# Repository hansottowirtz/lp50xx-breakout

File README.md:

# Breakout board for LP5018 and LP5024

- Designed with Autodesk Eagle
- 2-layer board
- Builtin 0603 R_IREF and trimpot to control current, and 1uF 0603 C_VCAP.
- Uses [LP50XX Library](./lp50xx.lbr), modified [Sparkfun Libraries](https://github.com/sparkfun/SparkFun-Eagle-Libraries) and a modified pinhead library.

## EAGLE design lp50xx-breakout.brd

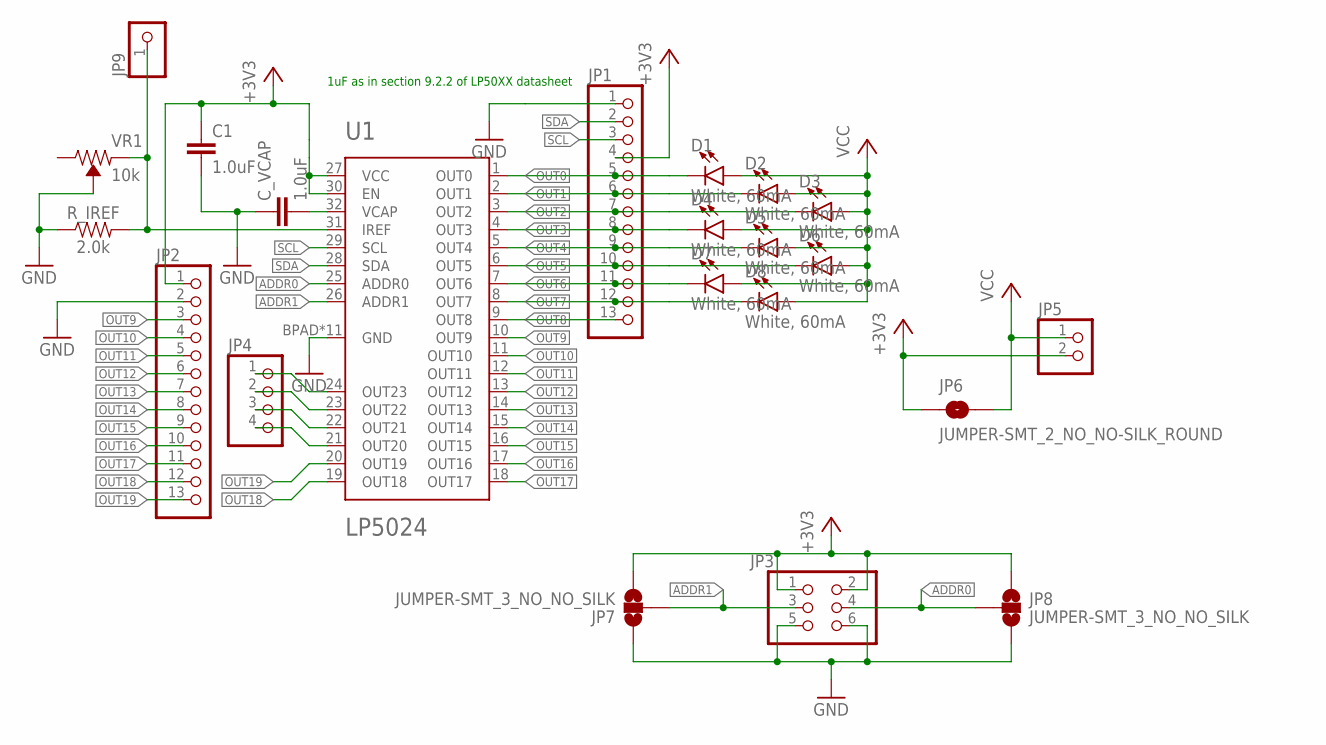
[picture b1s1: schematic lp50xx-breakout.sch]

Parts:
C1: 1.0uF; 0603
C_VCAP: 1.0uF; 0603
D1, D2, D3, D4, D5, D6, D7, D8: White, 60mA; SUPER_BRIGHT_SMD_LED_3014
JP1, JP2: PINHD-1X13; 1X13
JP3: PINHD-2X3; 2X03
JP4: PINHD-1X4; 1X04
JP5: PINHD-1X2; 1X02
JP6: JUMPER-SMT_2_NO_NO-SILK_ROUND; SMT-JUMPER_2_NO_NO-SILK_ROUND
JP7, JP8: JUMPER-SMT_3_NO_NO_SILK; SMT-JUMPER_3_0-NO_TRACE_NO-SILK
JP9: PINHD-1X1; 1X01
R_IREF: 2.0k; 0603
U1: LP5024; S-PVQFN-N32
VR1: 10k; TRIMPOT-SMD-3MM-CLOSED

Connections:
+3V3: C1.1, JP1.4, JP2.1, JP3.1, JP3.2, JP5.2, JP6.1, JP7.3, JP8.1, U1.27 (VCC), U1.30 (EN)
ADDR0: JP3.4, JP8.2, U1.25 (ADDR0)
ADDR1: JP3.3, JP7.2, U1.26 (ADDR1)
GND: C1.2, C_VCAP.1, JP1.1, JP2.2, JP3.5, JP3.6, JP7.1, JP8.3, R_IREF.1, U1.BPAD (GND), U1.EVIA@1 (GND), U1.EVIA@2 (GND), U1.EVIA@3 (GND), U1.EVIA@4 (GND), U1.EVIA@5 (GND), U1.EVIA@6 (GND), U1.EVIA@7 (GND), U1.EVIA@8 (GND), U1.EVIA@9 (GND), U1.TPAD (GND), VR1.2 (WIPER)
IREF: JP9.1, R_IREF.2, U1.31 (IREF), VR1.1 (CCW)
OUT0: D1.C, JP1.5, U1.1 (OUT0)
OUT1: D2.C, JP1.6, U1.2 (OUT1)
OUT2: D3.C, JP1.7, U1.3 (OUT2)
OUT3: D4.C, JP1.8, U1.4 (OUT3)
OUT4: D5.C, JP1.9, U1.5 (OUT4)
OUT5: D6.C, JP1.10, U1.6 (OUT5)
OUT6: D7.C, JP1.11, U1.7 (OUT6)
OUT7: D8.C, JP1.12, U1.8 (OUT7)
OUT8: JP1.13, U1.9 (OUT8)
OUT9: JP2.3, U1.10 (OUT9)
OUT10: JP2.4, U1.11 (OUT10)
OUT11: JP2.5, U1.12 (OUT11)
OUT12: JP2.6, U1.13 (OUT12)
OUT13: JP2.7, U1.14 (OUT13)
OUT14: JP2.8, U1.15 (OUT14)
OUT15: JP2.9, U1.16 (OUT15)
OUT16: JP2.10, U1.17 (OUT16)
OUT17: JP2.11, U1.18 (OUT17)
OUT18: JP2.12, U1.19 (OUT18)
OUT19: JP2.13, U1.20 (OUT19)
OUT20: JP4.4, U1.21 (OUT20)
OUT21: JP4.3, U1.22 (OUT21)
OUT22: JP4.2, U1.23 (OUT22)
OUT23: JP4.1, U1.24 (OUT23)
SCL: JP1.3, U1.29 (SCL)
SDA: JP1.2, U1.28 (SDA)
VCAP: C_VCAP.2, U1.32 (VCAP)
VCC: D1.A, D2.A, D3.A, D4.A, D5.A, D6.A, D7.A, D8.A, JP5.1, JP6.2

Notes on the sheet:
1uF as in section 9.2.2 of LP50XX datasheet

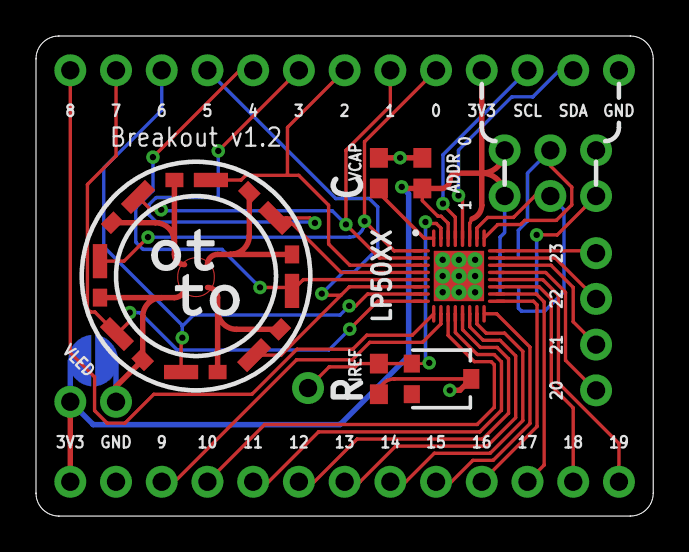
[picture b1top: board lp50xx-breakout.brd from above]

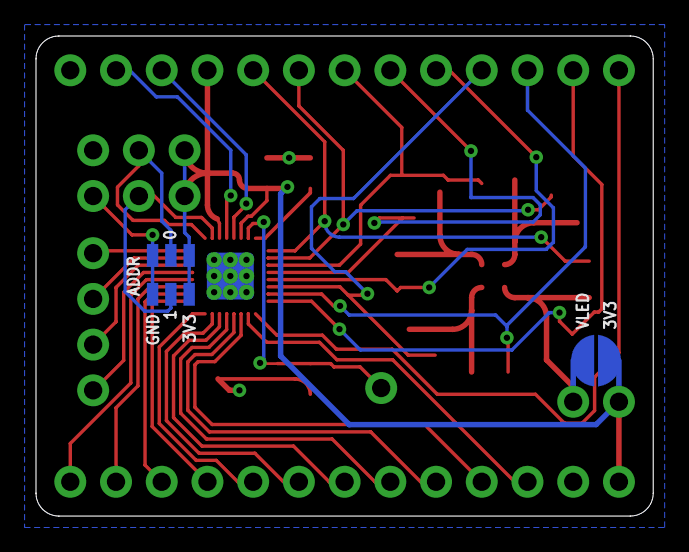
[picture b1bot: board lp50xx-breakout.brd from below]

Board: 2 copper layers, 34.3 x 26.7 mm, 22 parts (3 on the bottom side), 33 nets.

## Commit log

2019-01-27 Version 1.1
2019-02-16 Minor improvements
2023-03-05 Update design
2023-03-05 Add library, update readme

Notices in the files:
parts and their libraries:
SparkFun-Capacitors: Licensing: Creative Commons ShareAlike 4.0 International - https://creativecommons.org/licenses/by-sa/4.0
